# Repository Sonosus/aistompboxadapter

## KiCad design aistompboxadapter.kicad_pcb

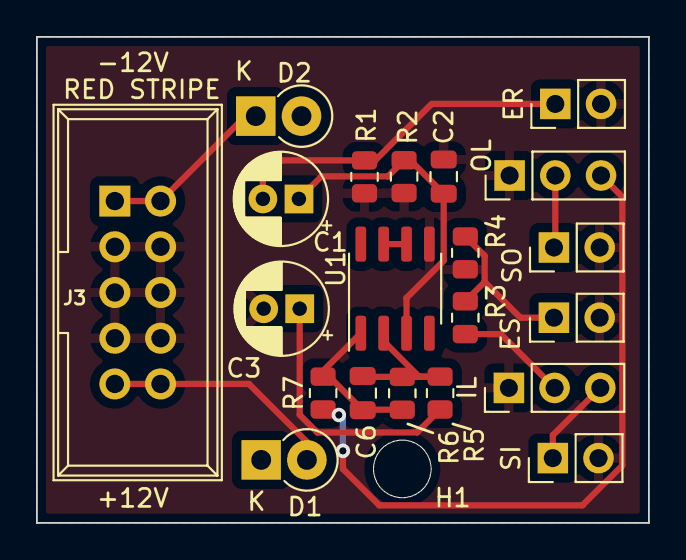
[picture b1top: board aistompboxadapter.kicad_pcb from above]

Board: 2 copper layers, 34.0 x 27.0 mm, 22 parts (0 on the bottom side), 16 nets.

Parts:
C1, C3: 10u; CP_Radial_D5.0mm_P2.00mm
C2: 10p; C_0805_2012Metric
C6: 47p; C_0805_2012Metric
D1, D2: 1N5817; D_DO-41_SOD81_P2.54mm_Vertical_KathodeUp
ER: FX RETURN; PinHeader_1x02_P2.54mm_Vertical
ES: FX SEND; PinHeader_1x02_P2.54mm_Vertical
H1: MountingHole; MountingHole_3.2mm_M3
IL: 100k; PinHeader_1x03_P2.54mm_Vertical
J3: Synth Power; Power_Header
OL: 100k; PinHeader_1x03_P2.54mm_Vertical
R1: 1M; R_0805_2012Metric
R2: 150k; R_0805_2012Metric
R3: 22k; R_0805_2012Metric
R4, R7: 1k; R_0805_2012Metric
R5: 470r; R_0805_2012Metric
R6: 10k; R_0805_2012Metric
SI: SI; PinHeader_1x02_P2.54mm_Vertical
SO: SYNTH OUT; PinHeader_1x02_P2.54mm_Vertical
U1: TL072; SOIC-8_3.9x4.9mm_P1.27mm

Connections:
+12V: D1.1 (K), U1.4 (V-)
-12V: D2.2 (A), U1.8 (V+)
GND: C2.2, C3.2, ER.2, ES.2, IL.1, J3.3, J3.4, J3.5, J3.6, J3.7, J3.8, OL.1, R1.1, R2.1, R4.1, SI.2, SO.2, U1.5 (+)
unnamed: C1.1, C2.1, R2.2, U1.3 (+)
unnamed: C1.2, ER.1, R1.2
unnamed: C3.1, R5.2
unnamed: C6.1, R5.1, R6.2, U1.2 (-)
unnamed: C6.2, R6.1, R7.2, U1.1
unnamed: D1.2 (A), J3.9, J3.10
unnamed: D2.1 (K), J3.1, J3.2
unnamed: IL.3, SI.1
unnamed: ES.1, R3.2, R4.2
unnamed: OL.2, SO.1
unnamed: IL.2, R3.1
unnamed: OL.3, R7.1
unnamed: U1.6 (-), U1.7

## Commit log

2022-01-09 add all files
2022-01-09 save board
2022-01-30 smd and add fab files
